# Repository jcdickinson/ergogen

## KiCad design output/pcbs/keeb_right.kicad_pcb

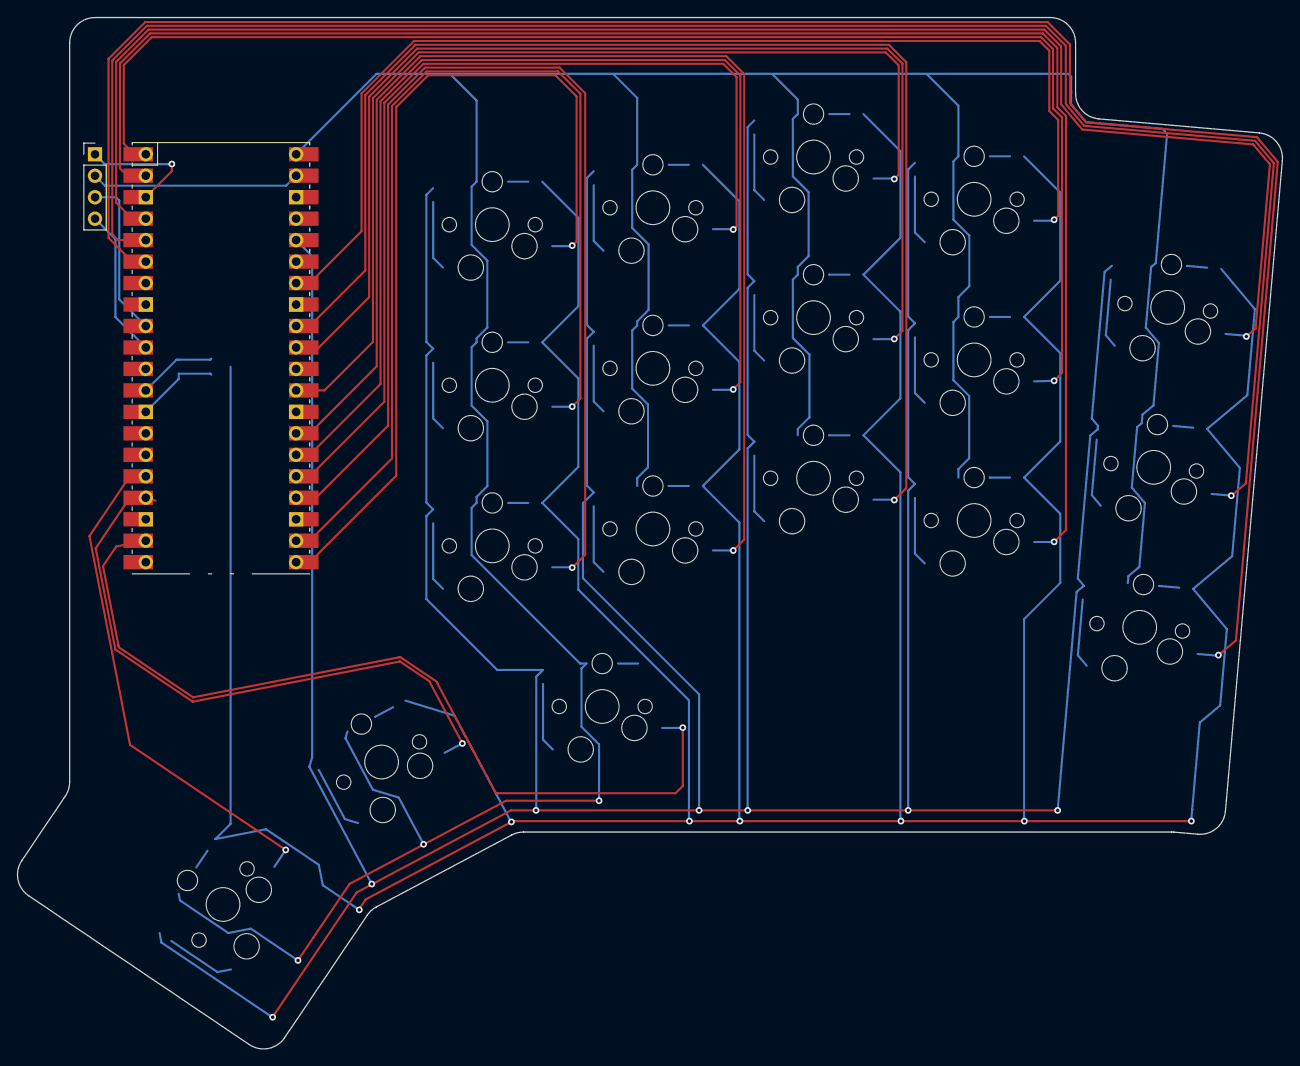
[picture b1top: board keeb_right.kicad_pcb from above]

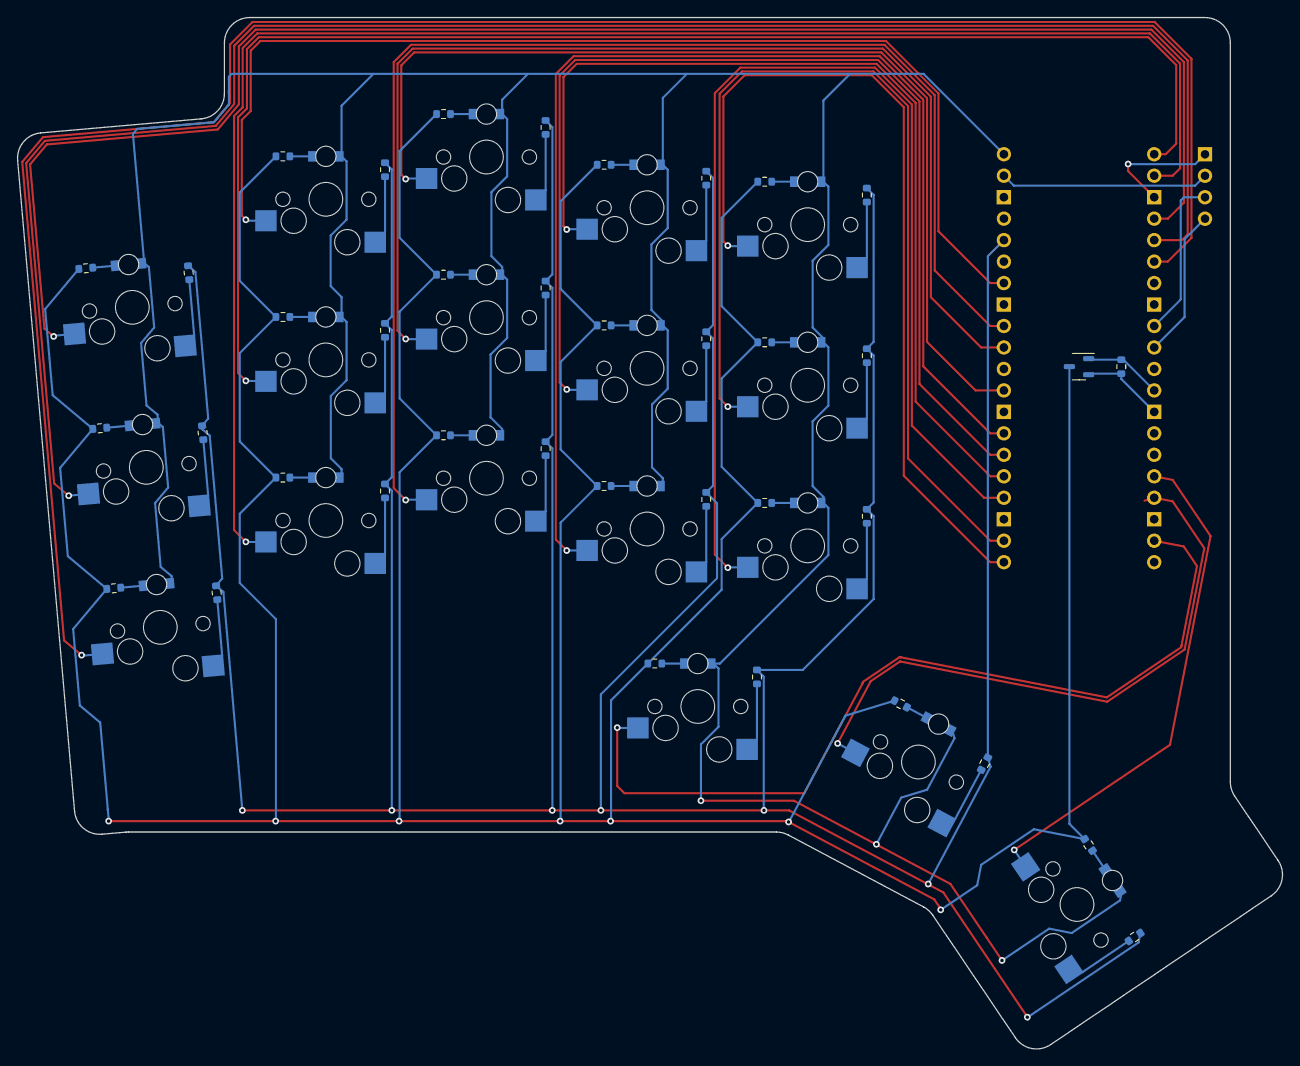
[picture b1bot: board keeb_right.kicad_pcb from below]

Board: 2 copper layers, 149.6 x 122.0 mm, 76 parts (38 on the bottom side), 62 nets.

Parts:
LED19, LED20, LED21, LED22, LED23, LED24, LED25, LED26, LED27, LED28, LED29, LED30, LED31, LED32, LED33, LED34, LED35, LED36: LED_1305_3412Metric
M2: SOT-23-3
MCU2: RPi_Pico_SMD_TH
R2, R39, R40, R41, R42, R43, R44, R45, R46, R47, R48, R49, R50, R51, R52, R53, R54, R55, R56, R57, R58, R59, R60, R61, R62, R63, R64, R65, R66, R67, R68, R69, R70, R71, R72, R73, R74: R_0603_1608Metric
S19, S20, S21, S22, S23, S24, S25, S26, S27, S28, S29, S30, S31, S32, S33, S34, S35, S36: MX
_2: PinHeader_1x04_P2.54mm_Vertical

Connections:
GND: M2.2, MCU2.3, MCU2.8, MCU2.13, MCU2.18, MCU2.23, MCU2.28, MCU2.38, R2.2, _2.1
LED_GATE: M2.1, MCU2.12, R2.1
LED_MOSFET_DRAIN: M2.3, R39.2, R40.2, R41.2, R42.2, R43.2, R44.2, R45.2, R46.2, R47.2, R48.2, R49.2, R50.2, R51.2, R52.2, R53.2, R54.2, R55.2, R56.2
MIRROR_SCL: MCU2.10, _2.4
MIRROR_SDA: MCU2.9, _2.3
V3: MCU2.36, R57.1, R58.1, R59.1, R60.1, R61.1, R62.1, R63.1, R64.1, R65.1, R66.1, R67.1, R68.1, R69.1, R70.1, R71.1, R72.1, R73.1, R74.1
VBUS: LED19.1, LED20.1, LED21.1, LED22.1, LED23.1, LED24.1, LED25.1, LED26.1, LED27.1, LED28.1, LED29.1, LED30.1, LED31.1, LED32.1, LED33.1, LED34.1, LED35.1, LED36.1, MCU2.40
VSYS: MCU2.39, _2.2
mirror_matrix_index_bottom: MCU2.27, S28.1
mirror_matrix_index_bottom_LED: LED28.2, R48.1
mirror_matrix_index_bottom_R: R66.2, S28.2
mirror_matrix_index_home: MCU2.26, S29.1
mirror_matrix_index_home_LED: LED29.2, R49.1
mirror_matrix_index_home_R: R67.2, S29.2
mirror_matrix_index_top: MCU2.25, S30.1
mirror_matrix_index_top_LED: LED30.2, R50.1
mirror_matrix_index_top_R: R68.2, S30.2
mirror_matrix_inner_bottom: MCU2.24, S31.1
mirror_matrix_inner_bottom_LED: LED31.2, R51.1
mirror_matrix_inner_bottom_R: R69.2, S31.2
mirror_matrix_inner_home: MCU2.22, S32.1
mirror_matrix_inner_home_LED: LED32.2, R52.1
mirror_matrix_inner_home_R: R70.2, S32.2
mirror_matrix_inner_top: MCU2.21, S33.1
mirror_matrix_inner_top_LED: LED33.2, R53.1
mirror_matrix_inner_top_R: R71.2, S33.2
mirror_matrix_middle_bottom: MCU2.32, S25.1
mirror_matrix_middle_bottom_LED: LED25.2, R45.1
mirror_matrix_middle_bottom_R: R63.2, S25.2
mirror_matrix_middle_home: MCU2.31, S26.1
mirror_matrix_middle_home_LED: LED26.2, R46.1
mirror_matrix_middle_home_R: R64.2, S26.2
mirror_matrix_middle_top: MCU2.29, S27.1
mirror_matrix_middle_top_LED: LED27.2, R47.1
mirror_matrix_middle_top_R: R65.2, S27.2
mirror_matrix_pinky_bottom: MCU2.6, S19.1
mirror_matrix_pinky_bottom_LED: LED19.2, R39.1
mirror_matrix_pinky_bottom_R: R57.2, S19.2
mirror_matrix_pinky_home: MCU2.5, S20.1
mirror_matrix_pinky_home_LED: LED20.2, R40.1
mirror_matrix_pinky_home_R: R58.2, S20.2
mirror_matrix_pinky_top: MCU2.4, S21.1
mirror_matrix_pinky_top_LED: LED21.2, R41.1
mirror_matrix_pinky_top_R: R59.2, S21.2
mirror_matrix_ring_bottom: MCU2.2, S22.1
mirror_matrix_ring_bottom_LED: LED22.2, R42.1
mirror_matrix_ring_bottom_R: R60.2, S22.2
mirror_matrix_ring_home: MCU2.1, S23.1
mirror_matrix_ring_home_LED: LED23.2, R43.1
mirror_matrix_ring_home_R: R61.2, S23.2
mirror_matrix_ring_top: MCU2.34, S24.1
mirror_matrix_ring_top_LED: LED24.2, R44.1
mirror_matrix_ring_top_R: R62.2, S24.2
mirror_thumbfan_far_thumb: MCU2.16, S36.1
mirror_thumbfan_far_thumb_LED: LED36.2, R56.1
mirror_thumbfan_far_thumb_R: R74.2, S36.2
mirror_thumbfan_home_thumb: MCU2.17, S35.1
mirror_thumbfan_home_thumb_LED: LED35.2, R55.1
mirror_thumbfan_home_thumb_R: R73.2, S35.2
mirror_thumbfan_near_thumb: MCU2.19, S34.1
mirror_thumbfan_near_thumb_LED: LED34.2, R54.1
mirror_thumbfan_near_thumb_R: R72.2, S34.2

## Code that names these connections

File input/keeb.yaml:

points:
    zones:
        matrix:
            key.bind: [0.5u, 0.5u, 0.5u, 0.5u]
            rotate: 5
            columns:
                pinky:
                    key.bind: [1u, 2u, 1.12u, 0.5u]
                ring:
                    key.splay: -5
                    key.origin: [-12, -19]
                    key.stagger: 12
                    key.bind: [1u, 5.5u, 1.6u, 0.5u]
                middle:
                    key.stagger: 5
                index:
                    key.stagger: -6
                inner:
                    key.stagger: -2
            rows:
                bottom:
                home:
                top:
        thumbfan:
            anchor:
                ref: matrix_inner_bottom
                shift: [-13, -19]
            columns:
                near:
                    key.bind: [0.5u, 1u, 0.65u, 3.5u]
                home:
                    key.spread: 23.25
                    key.splay: -28
                    key.origin: [-11.75, -9]
                    key.bind: [0.8u, 0.7u, 0.65u, 2u]
                far:
                    key.spread: 21.5
                    key.splay: -28
                    key.origin: [-10.7, -9]
                    key.bind: [1.06u, 0.5u, 0.65u, 2u]
            rows:
                thumb:
    mirror:
        ref: matrix_pinky_home
        distance: 300
outlines:
    keys:
        - what: rectangle
          operation: add
          where: true
          bound: true
          asym: both
          size: [5, 5]
    fillet:
        - what: outline
          name: keys
          asym: both
          fillet: 3
pcbs:
    keeb:
        outlines:
            main:
                outline: fillet
        footprints:
            led_mosfet_pulldown:
                what: r_0603
                asym: both
                where:
                    - ref: matrix_inner_home
                adjust:
                    shift: [37.1, 2.2]
                    rotate: 90
                params:
                    from: LED_GATE
                    to: GND
                    side: B
            led_mosfet:
                what: sot_23_3
                asym: left
                where:
                    - ref: matrix_inner_home
                adjust:
                    shift: [32.1, 2.2]
                    rotate: 180
                params:
                    gate: LED_GATE
                    drain: LED_MOSFET_DRAIN
                    source: GND
                    side: B
            led:
                what: led_1305
                where: meta.mirrored ~ false
                adjust:
                    shift: [0, 5.08]
                params:
                    from: '{{name}}_LED'
                    to: VBUS
            led_r:
                what: r_0603
                where: meta.mirrored ~ false
                adjust:
                    shift: [-5.08, 5.08]
                params:
                    to: '{{name}}_LED'
                    from: LED_MOSFET_DRAIN
                    side: B
            mx:
                what: mx
                where: meta.mirrored ~ false
                adjust:
                    rotate: 180
                params:
                    to: '{{name}}'
                    from: '{{name}}_R'
                    keycaps: true
                    hotswap: true
            mx_r:
                what: r_0603
                where: meta.mirrored ~ false
                adjust:
                    shift: [7, 3.5]
                    rotate: 90
                params:
                    from: '{{name}}_R'
                    to: V3
                    side: B
            i2c:
                what: pin_header_1x4
                asym: left
                where:
                    - ref: matrix_inner_top
                adjust:
                    shift: [47, 0.7]
                    rotate: 180
                params:
                    GND: GND
                    P1: VSYS
                    P2: SDA
                    P3: SCL
            mcu:
                what: rpi_pico
                asym: left
                where:
                    - ref: matrix_inner_home
                adjust:
                    shift: [32.1, 3.2]
                params:
                    VBUS: VBUS
                    VSYS: VSYS
                    V3: V3
                    GP2: matrix_pinky_top
                    GP1: matrix_pinky_home
                    GP0: matrix_pinky_bottom
                    GP5: matrix_ring_top
                    GP4: matrix_ring_home
                    GP3: matrix_ring_bottom
                    GP8: matrix_middle_top
                    GP7: matrix_middle_home
                    GP6: matrix_middle_bottom
                    GP11: matrix_index_top
                    GP10: matrix_index_home
                    GP9: matrix_index_bottom
                    GP14: matrix_inner_top
                    GP13: matrix_inner_home
                    GP13: matrix_inner_bottom
                    GP16: thumbfan_near_thumb
                    GP17: thumbfan_home_thumb
                    GP18: thumbfan_far_thumb
                    GP19: LED_GATE
                    GP26: SDA
                    GP27: SCL
            led_mirror:
                what: led_1305
                where: meta.mirrored ~ true
                adjust:
                    shift: [0, 5.08]
                params:
                    to: '{{name}}_LED'
                    from: VBUS
            led_r_mirror:
                what: r_0603
                where: meta.mirrored ~ true
                adjust:
                    shift: [-5.08, 5.08]
                params:
                    from: '{{name}}_LED'
                    to: LED_MOSFET_DRAIN
                    side: B
            mx_mirror:
                what: mx
                where: meta.mirrored ~ true
                adjust:
                    rotate: 180
                params:
                    from: '{{name}}'
                    to: '{{name}}_R'
                    keycaps: true
                    hotswap: true
            mx_r_mirror:
                what: r_0603
                where: meta.mirrored ~ true
                adjust:
                    shift: [7, 3.5]
                    rotate: 90
                params:
                    to: '{{name}}_R'
                    from: V3
                    side: B
            led_mosfet_mirror:
                what: sot_23_3
                asym: right
                where:
                    - ref: matrix_inner_home
                adjust:
                    shift: [32.1, 2.2]
                params:
                    gate: LED_GATE
                    drain: LED_MOSFET_DRAIN
                    source: GND
                    side: B
            i2c_mirror:
                what: pin_header_1x4
                asym: right
                where:
                    - ref: matrix_inner_top
                adjust:
                    shift: [47, 8.32]
                params:
                    GND: GND
                    P1: VSYS
                    P2: MIRROR_SDA
                    P3: MIRROR_SCL
            mcu_mirror:
                what: rpi_pico
                asym: right
                where:
                    - ref: matrix_inner_home
                adjust:
                    shift: [32.1, 3.2]
                params:
                    VBUS: VBUS
                    VSYS: VSYS
                    V3: V3
                    GP4: mirror_matrix_pinky_bottom
                    GP3: mirror_matrix_pinky_home
                    GP2: mirror_matrix_pinky_top
                    GP1: mirror_matrix_ring_bottom
                    GP0: mirror_matrix_ring_home
                    GP28: mirror_matrix_ring_top
                    GP27: mirror_matrix_middle_bottom
                    GP26: mirror_matrix_middle_home
                    GP22: mirror_matrix_middle_top
                    GP21: mirror_matrix_index_bottom
                    GP20: mirror_matrix_index_home
                    GP19: mirror_matrix_index_top
                    GP18: mirror_matrix_inner_bottom
                    GP17: mirror_matrix_inner_home
                    GP16: mirror_matrix_inner_top
                    GP12: mirror_thumbfan_far_thumb
                    GP13: mirror_thumbfan_home_thumb
                    GP14: mirror_thumbfan_near_thumb
                    GP9: LED_GATE
                    GP6: MIRROR_SDA
                    shift: [7, 3.5]
                    rotate: 90
                    GP7: MIRROR_SCL

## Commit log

2023-08-14 feat: add reversible kailh footprint
2023-08-19 add all files
